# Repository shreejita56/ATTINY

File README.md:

# ATTINY

I made a small devboard based on Atinny1616-S .It has inbuild 3.3V voltage regulator and a USB-to-UART serial convertor  .Power and data comes from USB-C . The board has an inbuilt LED. and has 8 pin outlet in which 1 is gnd,  1 is power and another 6 are general out pin pins connected to the MCU. The Devboard was designed on kicad . 

## Features
- Based on Atinny1616-S
- uses USB-C for Power and data
- has onboard 3.3V Regulator
- has onboard USB-to-UART serial convertor IC (ch340X)
- has 8 outlet pins (6 connected to MCU ,1 GND ,1 Power)

## BOM

| **Designation** | **Comment** | **Quantity** | **Price ($)** | **Link** |
| :-------------- | :---------- | :----------- | :------------ | :------- |
| C1, C2, C4 | 1uF | 6 | 0.1326 | [JLCPCB](https://jlcpcb.com/partdetail/54083-CL03A105MQ3CSNH/C53067) |
| C3, C5 | 100nF (0.1uF) | 4 | 0.1760 | [JLCPCB](https://jlcpcb.com/partdetail/50070-CL03A104KP3NNNC/C49062) |
| D1 | LED | 2 | 0.6900 | [JLCPCB](https://jlcpcb.com/partdetail/XINGLIGHT-XL0201SURC/C3646923) |
| R1, R2 | 5.1k | 4 | 0.0740 | [JLCPCB](https://jlcpcb.com/partdetail/LIZElec-CR0201FH5101G/C100142) |
| R3, R4 | 1k | 4 | 0.1520 | [JLCPCB](https://jlcpcb.com/partdetail/LIZElec-CR0201FH1001G/C100125) |
| U1 | XC6206PxxxMR | 2 | 0.7850 | [JLCPCB](https://jlcpcb.com/partdetail/TorexSemicon-XC6206P252MR/C15906) |
| U2 | ATtiny1616-S | 2 | 5.3754 | [JLCPCB](https://jlcpcb.com/partdetail/MicrochipTech-ATTINY1616SN/C614136) |
| U3 | CH340X | 2 | 1.3668 | [JLCPCB](https://jlcpcb.com/partdetail/WCH_Jiangsu_Qin_Heng-CH340X/C3035748) |
| | **Component Total** | | **8.7518** | |
| | Setup | | 25.00 | |
| | Loader/Assembly/Setup Fee | | 12.57 | |
| | PCB | | 4.00 | |
| | Shipping | | 11.17 | |
| | **Grand Total** | | **61.4918** | |

## Schematics

## PCB

## CAD

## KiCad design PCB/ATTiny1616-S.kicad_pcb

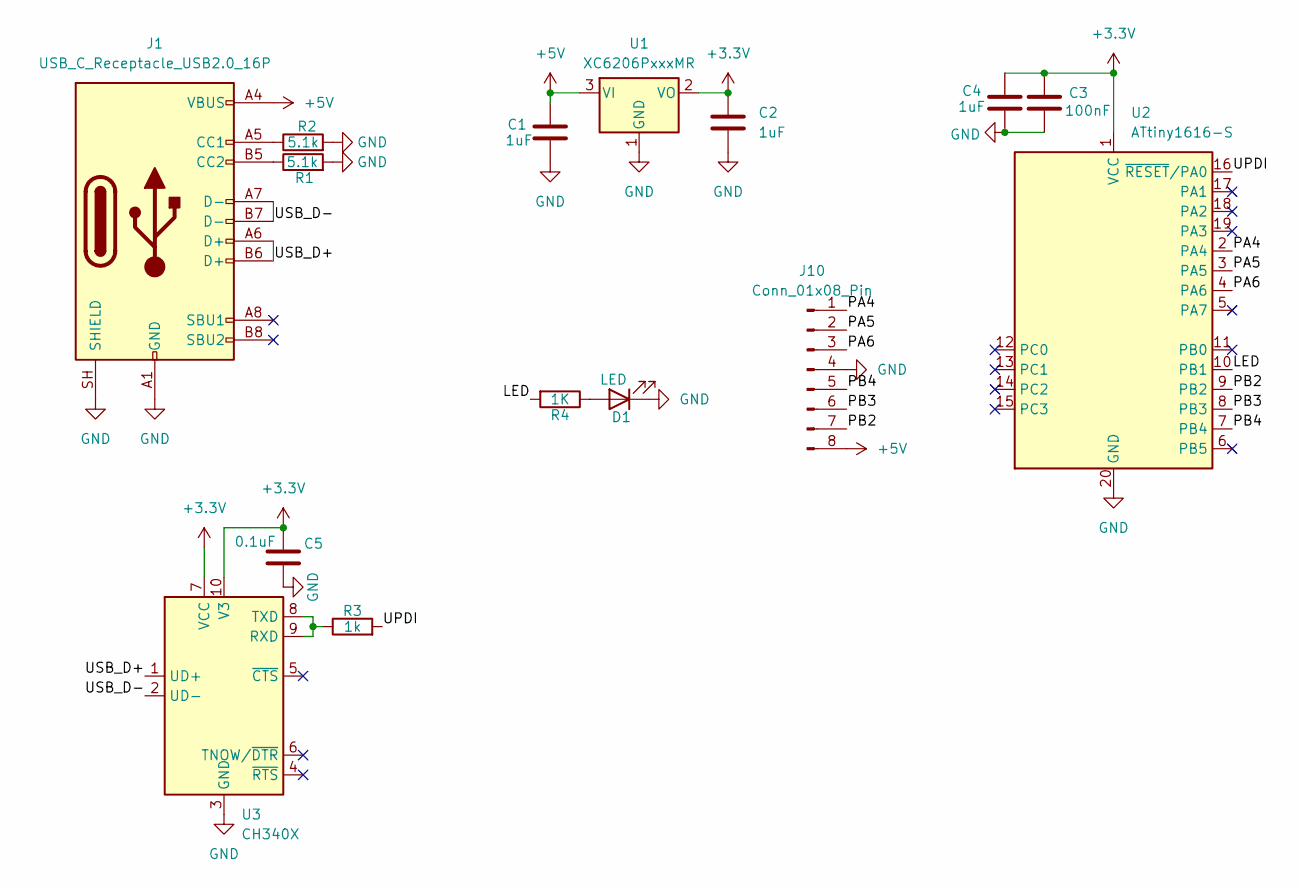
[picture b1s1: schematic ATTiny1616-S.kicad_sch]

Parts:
C1, C2, C4: 1uF; C_0201_0603Metric; LCSC Part C1620132
C3: 100nF; C_0201_0603Metric; LCSC Part C907942
C5: 0.1uF; C_0201_0603Metric; LCSC Part C2979769
D1: LED; LED_0201_0603Metric
J1: USB_C_Receptacle_USB2.0_16P; USB_C_Receptacle_HRO_TYPE-C-31-M-12; LCSC Part C2765186
J10: Conn_01x08_Pin; PinHeader_1x08_P2.54mm_Vertical_SMD_Pin1Right
R1, R2: 5.1k; R_0201_0603Metric; LCSC Part C1366782
R3: 1k; R_0201_0603Metric; LCSC Part C1364628
R4: 1K; R_0201_0603Metric
U1: XC6206PxxxMR; SOT-23-3; LCSC Part C136701
U2: ATtiny1616-S; SOIC-20_L13.0-W7.6-P1.27-LS10.3-BL; LCSC Part C614136
U3: CH340X; MSOP-10_3x3mm_P0.5mm; LCSC Part C3035748

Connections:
+3.3V: C2.1, C3.1, C4.1, C5.1, U1.2 (VO), U2.1 (VCC), U3.7 (VCC), U3.10 (V3)
+5V: C1.1, J1.A4 (VBUS), J1.A9 (VBUS), J1.B4 (VBUS), J1.B9 (VBUS), J10.8, U1.3 (VI)
/LED: R4.2, U2.10 (PB1)
/PA4: J10.1, U2.2 (PA4)
/PA5: J10.2, U2.3 (PA5)
/PA6: J10.3, U2.4 (PA6)
/PB2: J10.7, U2.9 (PB2)
/PB3: J10.6, U2.8 (PB3)
/PB4: J10.5, U2.7 (PB4)
/UPDI: R3.2, U2.16 (~RESET/PA0)
/USB_D+: J1.A6 (D+), J1.B6 (D+), U3.1 (UD+)
/USB_D-: J1.A7 (D-), J1.B7 (D-), U3.2 (UD-)
GND: C1.2, C2.2, C3.2, C4.2, C5.2, D1.1 (K), J1.A1 (GND), J1.A12 (GND), J1.B1 (GND), J1.B12 (GND), J1.SH (SHIELD), J10.4, R1.2, R2.2, U1.1 (GND), U2.20 (GND), U3.3 (GND)
unnamed: D1.2 (A), R4.1
unnamed: J1.A5 (CC1), R2.1
unnamed: J1.B5 (CC2), R1.1
unnamed: R3.1, U3.8 (TXD), U3.9 (RXD)

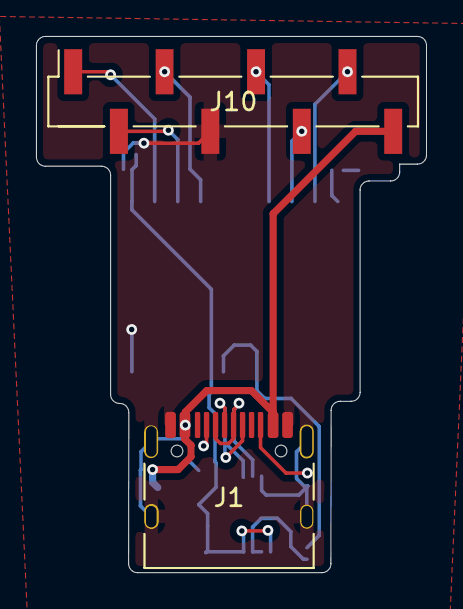
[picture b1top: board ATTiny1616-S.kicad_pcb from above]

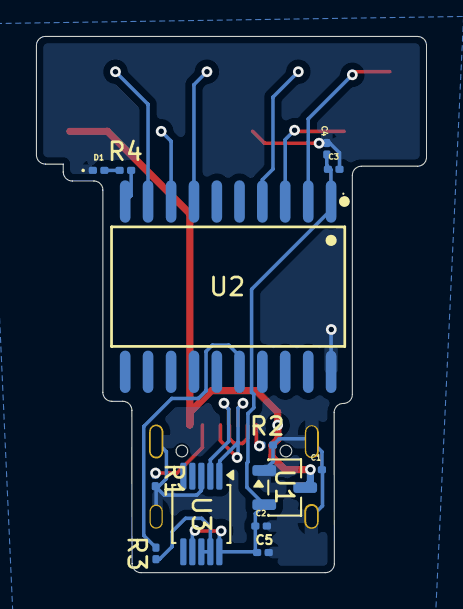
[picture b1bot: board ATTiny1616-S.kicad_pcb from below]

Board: 2 copper layers, 21.7 x 29.8 mm, 15 parts (13 on the bottom side), 17 nets.

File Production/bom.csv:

Designator,Footprint,Quantity,Value,LCSC Part #
"C1, C2, C4",0201,3,1uF,C1620132
C3,0201,1,100nF,C907942
C5,0201,1,0.1uF,C2979769
D1,0201,1,LED,
J1,USB_C_Receptacle_HRO_TYPE-C-31-M-12,1,USB_C_Receptacle_USB2.0_16P,C2765186
J10,PinHeader_1x08_P2.54mm_Vertical_SMD_Pin1Right,1,Conn_01x08_Pin,
"R1, R2",0201,2,5.1k,C1366782
R3,0201,1,1k,C1364628
R4,0201,1,1K,
U1,SOT-23-3,1,XC6206PxxxMR,C136701
U2,SOIC-20_L13.0-W7.6-P1.27-LS10.3-BL,1,ATtiny1616-S,C614136
U3,MSOP-10_3x3mm_P0.5mm,1,CH340X,C3035748
